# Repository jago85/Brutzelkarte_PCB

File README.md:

# Brutzelkarte_PCB
Brutzelkarte - N64 Flash Cart PCB (KiCad)

# IMPORTANT!
This project does not support piracy! You are only allowed to play games you own yourself and you have to create your own ROM images.

## Features
* Open Source hardware and software
* no BGA packages (DIY friendly)
* no original chips from victim modules needed
* FPGA based logic
  * Lattice LCMXO2-7000HC-6TG144C
  * flexible (everything goes through the FPGA)
  * updatable (internal FLASH can be updated over UART)
  * expandable (free ressources for new features)
* 64 MiB (512 MBit) QSPI FLASH for ROMs
  * can be split into multiple parts for smaller ROMs
  * download is slow compared to SD card based carts
  * once a ROM is flashed the boot is as fast as the original module (no need to select and load the game every startup if you want to focus on a specific game)
  * can be expanded in the future (QSPI FLASH chips can use the same pinout for bigger memory because they don't need additional address lines)
* 8 MiB (64 MBit) dedicated for cart menu
* 256 KiB battery backed up SRAM for savegames
  * SRAM can be split into multiple savegames
  * emulates all cart based savegames
    * EEPROM 4 KBit 
	* EEPROM 16 KBit
	* SRAM 256 KBit
	* SRAM 3x 256 KBit
	* FlashRam 1 MBit
* RTC
  * only used by Animal Forest
* integrated FT232RL USB-UART
  * direct UART TTL connections if you want to save the money for the FT232RL

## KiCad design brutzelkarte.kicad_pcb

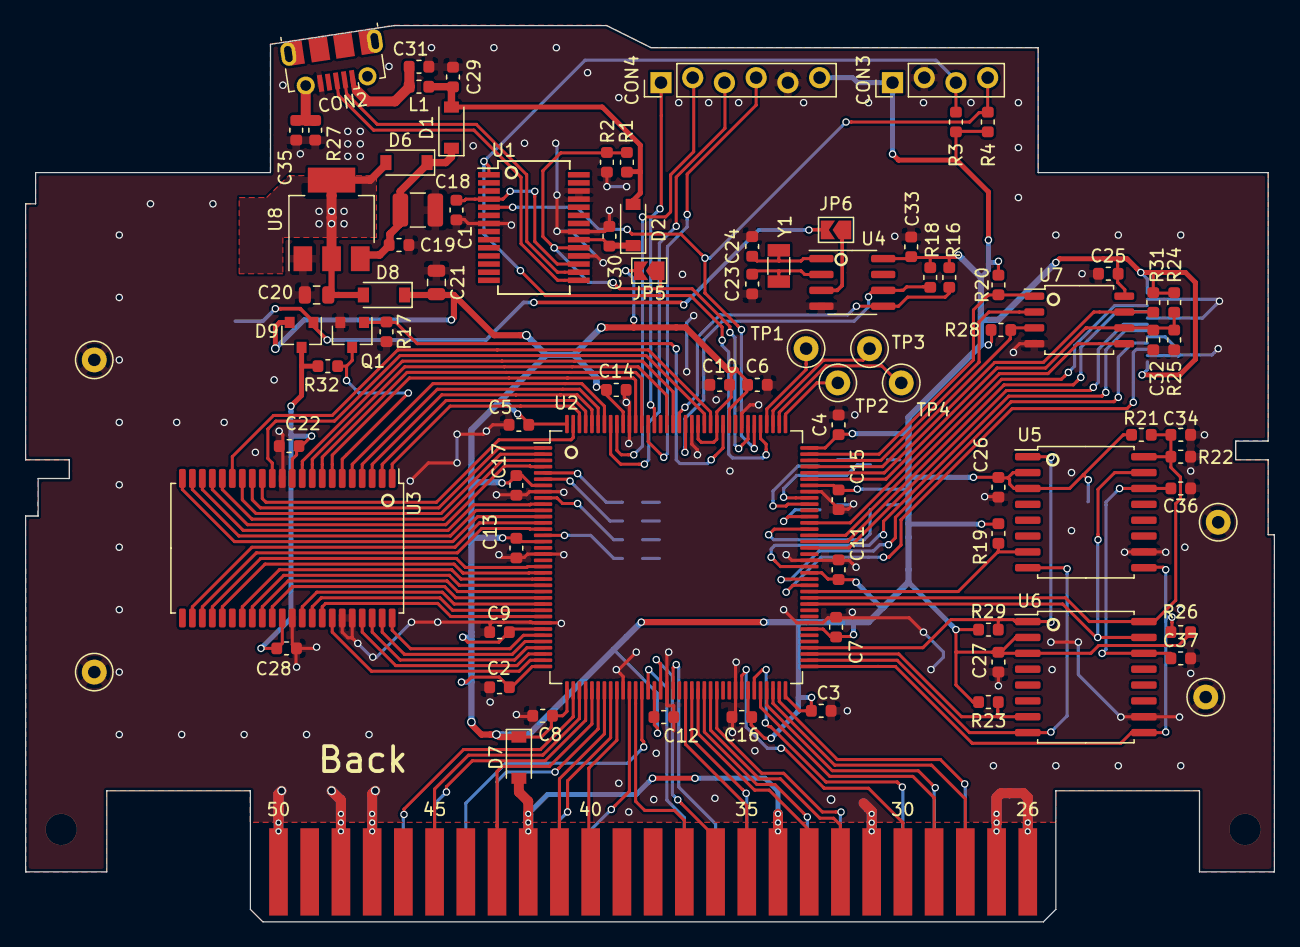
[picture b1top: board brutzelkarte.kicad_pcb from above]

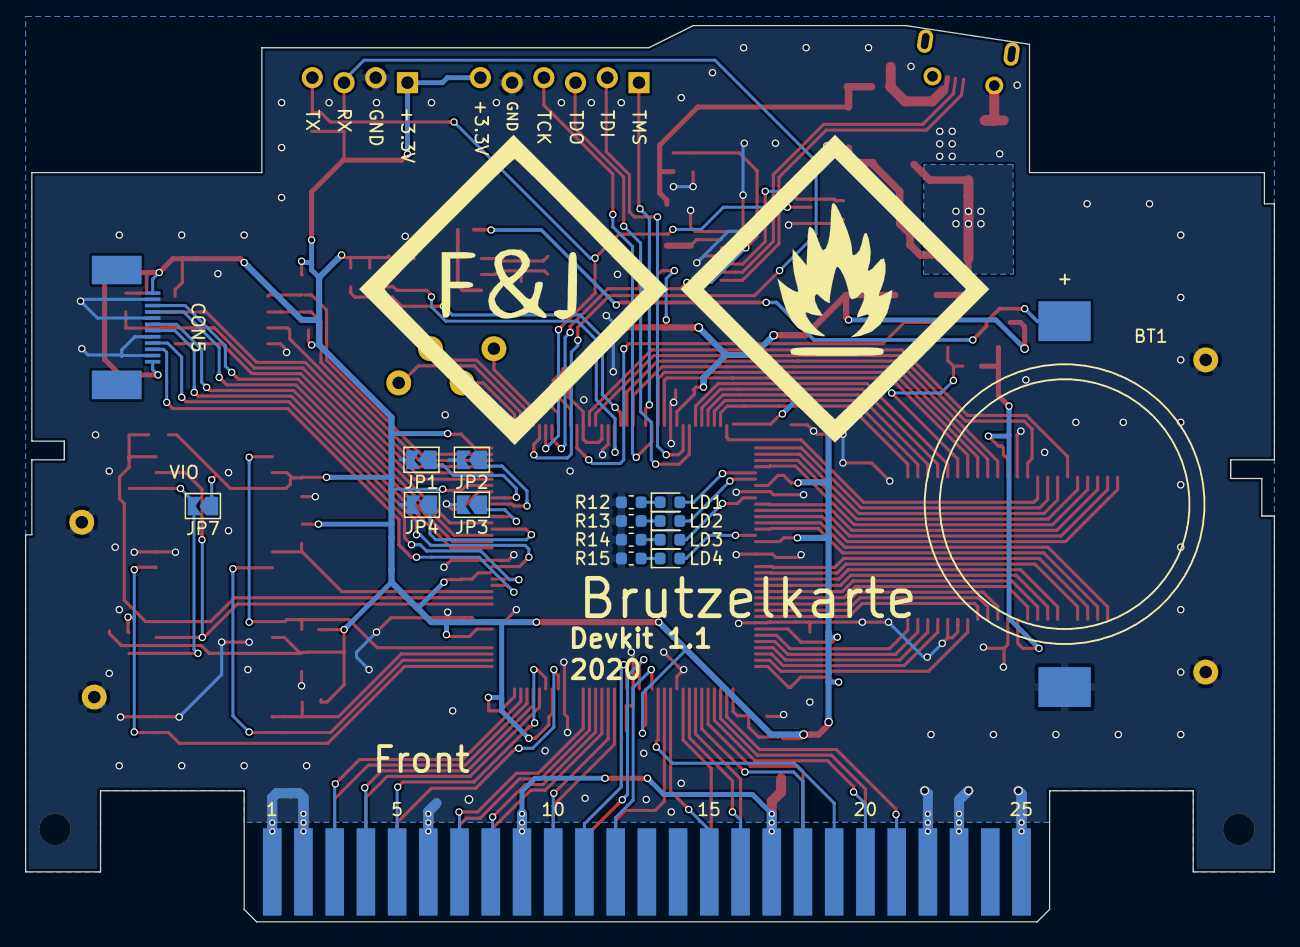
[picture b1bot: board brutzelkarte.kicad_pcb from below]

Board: 2 copper layers, 100.0 x 71.8 mm, 103 parts (16 on the bottom side), 125 nets.

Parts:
BT1: Battery_Cell; BU2032SM
C1, C2, C3, C4, C5, C6, C7, C8, C9, C10, C11, C12, C13, C14, C15, C16, C17, C19, C22, C25, C26, C27, C28, C30, C33, C36, C37: 100n; C_0603_1608Metric
C18: 10u; C_1210_3225Metric
C20: 1u; C_0805_2012Metric
C21: 47u; C_0805_2012Metric
C23, C24: 6-9 pF; C_0603_1608Metric
C29: 4u7; C_0603_1608Metric
C31, C35: 10n; C_0603_1608Metric
C32, C34: ?n; C_0603_1608Metric
CON1: N64-Cartridge; N64-Connector
CON2: USB_B_Micro; USB_Micro-B_Molex-105017-0001
CON3: Conn_01x04; PinHeader_1x04_P2.54mm_NoSolder
CON4: Conn_01x06; PinHeader_1x06_P2.54mm_NoSolder
CON5: Conn_01x12; 12pinFPC_ConnectorP0.5mm
D1, D2, D6, D7, D8: D_Schottky_Small; D_SOD-123
D9: BAT54C; SOT-23
GND1, GND2, GND3, GND4: TestPoint; TestPoint_Loop_D2.50mm_Drill1.0mm
JP1, JP2, JP3, JP4, JP5, JP6, JP7: SolderJumper_2_Open; SolderJumper-2_P1.3mm_Open_TrianglePad1.0x1.5mm
L1: Ferrite; L_0603_1608Metric
LD1, LD2, LD3, LD4: LED_Small; LED_0603_1608Metric
Q1: BSS138K; SOT-23
R1: 6k8; R_0603_1608Metric
R2, R3, R4, R19, R20, R21, R22, R23, R24, R25, R26, R28, R29, R31, R32: 10k; R_0603_1608Metric
R12, R13, R14, R15: 330; R_0603_1608Metric
R16, R18: 4k7; R_0603_1608Metric
R17: 2k2; R_0603_1608Metric
R27: 100k; R_0603_1608Metric
TP1, TP2, TP3, TP4: TestPoint; TestPoint_Loop_D2.50mm_Drill1.0mm
U1: FT232RL; SSOP-28_5.3x10.2mm_P0.65mm
U2: LCMXO2-7000Hx-xTG144x; TQFP-144_20x20mm_P0.5mm
U3: IS62WV12816EBLL; TSOP-II-44_10.16x18.41mm_P0.8mm
U4: MCP7940N; SOIC-8_3.9x4.9mm_P1.27mm
U5, U6: S25FL256S; SOIC-16W_7.5x10.3mm_P1.27mm
U7: W25Q_SOIC8; SOIC-8_5.275x5.275mm_P1.27mm
U8: TLV1117LV; SOT-223
Y1: 32768; Crystal_SMD_3215-2Pin_3.2x1.5mm

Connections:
+3V3: C2.1, C3.1, C4.1, C5.1, C6.1, C7.1, C8.1, C9.1, C10.1, C11.1, C12.1, C13.1, C14.1, C15.1, C16.1, C17.1, C21.1, C25.2, C26.1, C27.1, C33.1, CON3.1, CON4.6, CON5.1, CON5.12, D7.1, D8.1, D9.2, JP5.2, JP7.1, R3.1, R4.1, R16.1, R18.1, R19.1, R20.1, R21.1, R23.1, R24.1, R26.1, R28.1, R29.1, R31.1, U2.7, U2.16, U2.30, U2.36, U2.37, U2.51, U2.66, U2.72, U2.79, U2.88, U2.102, U2.108, U2.118, U2.120, U2.123, U2.135, U2.144, U4.8, U5.2, U5.3, U6.2, U6.3, U7.8
/fpga/BOOT_CS: R20.2, U2.107, U7.1
/fpga/BOOT_IO0: U2.96, U7.5
/fpga/BOOT_IO1: U2.106, U7.2
/fpga/BOOT_IO2: R28.2, U2.105, U7.3
/fpga/BOOT_IO3: R31.2, U2.104, U7.7
/fpga/BOOT_SCK: C32.1, R24.2, R25.1, U2.103, U7.6
/fpga/EXT0: CON5.3, U2.94
/fpga/EXT1: CON5.4, U2.93
/fpga/EXT2: CON5.6, U2.92
/fpga/EXT3: CON5.7, U2.89
/fpga/EXT4: CON5.9, U2.87
/fpga/EXT5: CON5.10, U2.86
/fpga/JP1: JP1.1, U2.100
/fpga/JP2: JP2.1, U2.99
/fpga/JP3: JP3.1, U2.97
/fpga/JP4: JP4.1, U2.95
/fpga/LED1: LD1.2, U2.5
/fpga/LED2: LD2.2, U2.6
/fpga/LED3: LD3.2, U2.9
/fpga/LED4: LD4.2, U2.15
/fpga/N64_AD0: CON1.28, U2.70
/fpga/N64_AD1: CON1.29, U2.68
/fpga/N64_AD2: CON1.30, U2.65
/fpga/N64_AD3: CON1.32, U2.60
/fpga/N64_AD4: CON1.36, U2.52
/fpga/N64_AD5: CON1.37, U2.48
/fpga/N64_AD6: CON1.40, U2.45
/fpga/N64_AD7: CON1.41, U2.43
/fpga/N64_AD8: CON1.16, U2.44
/fpga/N64_AD9: CON1.15, U2.47
/fpga/N64_AD10: CON1.12, U2.50
/fpga/N64_AD11: CON1.11, U2.54
/fpga/N64_AD12: CON1.7, U2.61
/fpga/N64_AD13: CON1.5, U2.67
/fpga/N64_AD14: CON1.4, U2.69
/fpga/N64_AD15: CON1.3, U2.71
/fpga/N64_ALEH: CON1.35, U2.56
/fpga/N64_ALEL: CON1.33, U2.58
/fpga/N64_CIC_DCLK: CON1.43, U2.41
/fpga/N64_CIC_DIO: CON1.18, U2.42
/fpga/N64_CR: CON1.20, U2.40
/fpga/N64_EEP_SDAT: CON1.21, U2.38
/fpga/N64_NMI: CON1.45, U2.39
/fpga/N64_READ: CON1.10, U2.57
/fpga/N64_SI_CLK: CON1.19, U2.49
/fpga/N64_VCC: CON1.9, CON1.17, CON1.34, CON1.42, D7.2
/fpga/N64_WRITE: CON1.8, U2.59
/fpga/RAM_A0: U2.138, U3.5
/fpga/RAM_A1: U2.139, U3.4
/fpga/RAM_A2: U2.140, U3.3
/fpga/RAM_A3: U2.141, U3.2
/fpga/RAM_A4: U2.142, U3.1
/fpga/RAM_A5: U2.31, U3.44
/fpga/RAM_A6: U2.32, U3.43
/fpga/RAM_A7: U2.33, U3.42
/fpga/RAM_A8: U2.21, U3.27
/fpga/RAM_A9: U2.20, U3.26
/fpga/RAM_A10: U2.14, U3.25
/fpga/RAM_A11: U2.13, U3.24
/fpga/RAM_A12: U2.12, U3.22
/fpga/RAM_A13: U2.11, U3.21
/fpga/RAM_A14: U2.10, U3.20
/fpga/RAM_A15: U2.4, U3.19
/fpga/RAM_A16: U2.3, U3.18
/fpga/RAM_CE: Q1.1, R17.1, U2.119
/fpga/RAM_DQ0: U2.133, U3.7
/fpga/RAM_DQ1: U2.132, U3.8
/fpga/RAM_DQ2: U2.128, U3.9
/fpga/RAM_DQ3: U2.127, U3.10
/fpga/RAM_DQ4: U2.122, U3.13
/fpga/RAM_DQ5: U2.143, U3.14
/fpga/RAM_DQ6: U2.1, U3.15
/fpga/RAM_DQ7: U2.2, U3.16
/fpga/RAM_DQ8: U2.22, U3.29
/fpga/RAM_DQ9: U2.23, U3.30
/fpga/RAM_DQ10: U2.24, U3.31
/fpga/RAM_DQ11: U2.25, U3.32
/fpga/RAM_DQ12: U2.26, U3.35
/fpga/RAM_DQ13: U2.27, U3.36
/fpga/RAM_DQ14: U2.28, U3.37
/fpga/RAM_DQ15: U2.35, U3.38
/fpga/RAM_OE: U2.34, U3.41
/fpga/RAM_WE: U2.121, U3.17
/fpga/ROM_CS0: R19.2, U2.85, U5.7
/fpga/ROM_CS1: R23.2, U2.75, U6.7
/fpga/ROM_IO0: U2.83, U5.15, U6.15
/fpga/ROM_IO1: U2.74, U5.8, U6.8
/fpga/ROM_IO2: R26.2, U2.73, U5.9, U6.9
/fpga/ROM_IO3: R29.2, U2.76, U5.1, U6.1
/fpga/ROM_SCK: C34.1, R21.2, R22.1, U2.84, U5.16, U6.16
/fpga/RTC_SCL: R18.2, U2.125, U4.6
/fpga/RTC_SDA: R16.2, U2.126, U4.5
/fpga/TCK: CON4.4, U2.131
/fpga/TDI: CON4.2, U2.136
/fpga/TDO: CON4.3, U2.137
/fpga/TEST1: TP1.1, U2.112
/fpga/TEST2: TP2.1, U2.109
/fpga/TEST3: TP3.1, U2.111
/fpga/TEST4: TP4.1, U2.110
/fpga/TMS: CON4.1, U2.130
/fpga/UART_RX: CON3.3, R3.2, U1.1, U2.113
/fpga/UART_TX: CON3.4, R4.2, U1.5, U2.114
/fpga/USB_DETECT: JP5.1, R1.2, R2.1, U1.19, U2.115
/memory/RAM_CS: Q1.3, R32.2, U3.6
/memory/RAM_VDD: C22.1, C28.1, D9.3, R32.1, U3.11, U3.33
/memory/ROM_VIO: C36.1, C37.1, JP7.2, U5.14, U6.14
/memory/VBAT: BT1.1, D9.1, JP6.2
/memory/VBAT_JP: JP6.1, U4.3
/power/+3V3_REG: C20.1, D6.2, D8.2, U8.2, U8.4
/power/USB_VCC: C18.1, C19.1, D1.1, D6.1, U8.3
/usb_uart/FTDI_VCC: C30.1, D2.1, U1.20
/usb_uart/FT_3V3: C1.2, U1.4, U1.17
/usb_uart/USBD+: CON2.3, U1.15
/usb_uart/USBD-: CON2.2, U1.16
/usb_uart/USB_VBUS: C29.1, D1.2, D2.2, L1.1, R1.1
/usb_uart/VBUS: C31.1, CON2.1, L1.2
GND: BT1.2, C1.1, C2.2, C3.2, C4.2, C5.2, C6.2, C7.2, C8.2, C9.2, C10.2, C11.2, C12.2, C13.2, C14.2, C15.2, C16.2, C17.2, C18.2, C19.2, C20.2, C21.2, C22.2, C23.2, C24.2, C25.1, C26.2, C27.2, C28.2, C29.2, C30.2, C31.2, C32.2, C33.2, C34.2, C35.2, C36.2, C37.2, CON1.1, CON1.2, CON1.6, CON1.22, CON1.23, CON1.25, CON1.26, CON1.27, CON1.31, CON1.47, CON1.48, CON1.50, CON2.5, CON3.2, CON4.5, CON5.2, CON5.5, CON5.8, CON5.11, GND1.1, GND2.1, GND3.1, GND4.1, JP1.2, JP2.2, JP3.2, JP4.2, Q1.2, R2.2, R12.2, R13.2, R14.2, R15.2, R17.2, R22.2, R25.2, R27.2, U1.7, U1.18, U1.21, U1.25, U1.26, U2.8, U2.18, U2.29, U2.46, U2.53, U2.64, U2.80, U2.90, U2.101, U2.116, U2.124, U2.134, U3.12, U3.34, U3.39, U3.40, U4.4, U5.10, U6.10, U7.4, U8.1
unnamed: C23.1, U4.2, Y1.2
unnamed: C24.1, U4.1, Y1.1
unnamed: C35.1, CON2.6, R27.1
unnamed: LD1.1, R12.1
unnamed: LD2.1, R13.1
unnamed: LD3.1, R14.1
unnamed: LD4.1, R15.1
